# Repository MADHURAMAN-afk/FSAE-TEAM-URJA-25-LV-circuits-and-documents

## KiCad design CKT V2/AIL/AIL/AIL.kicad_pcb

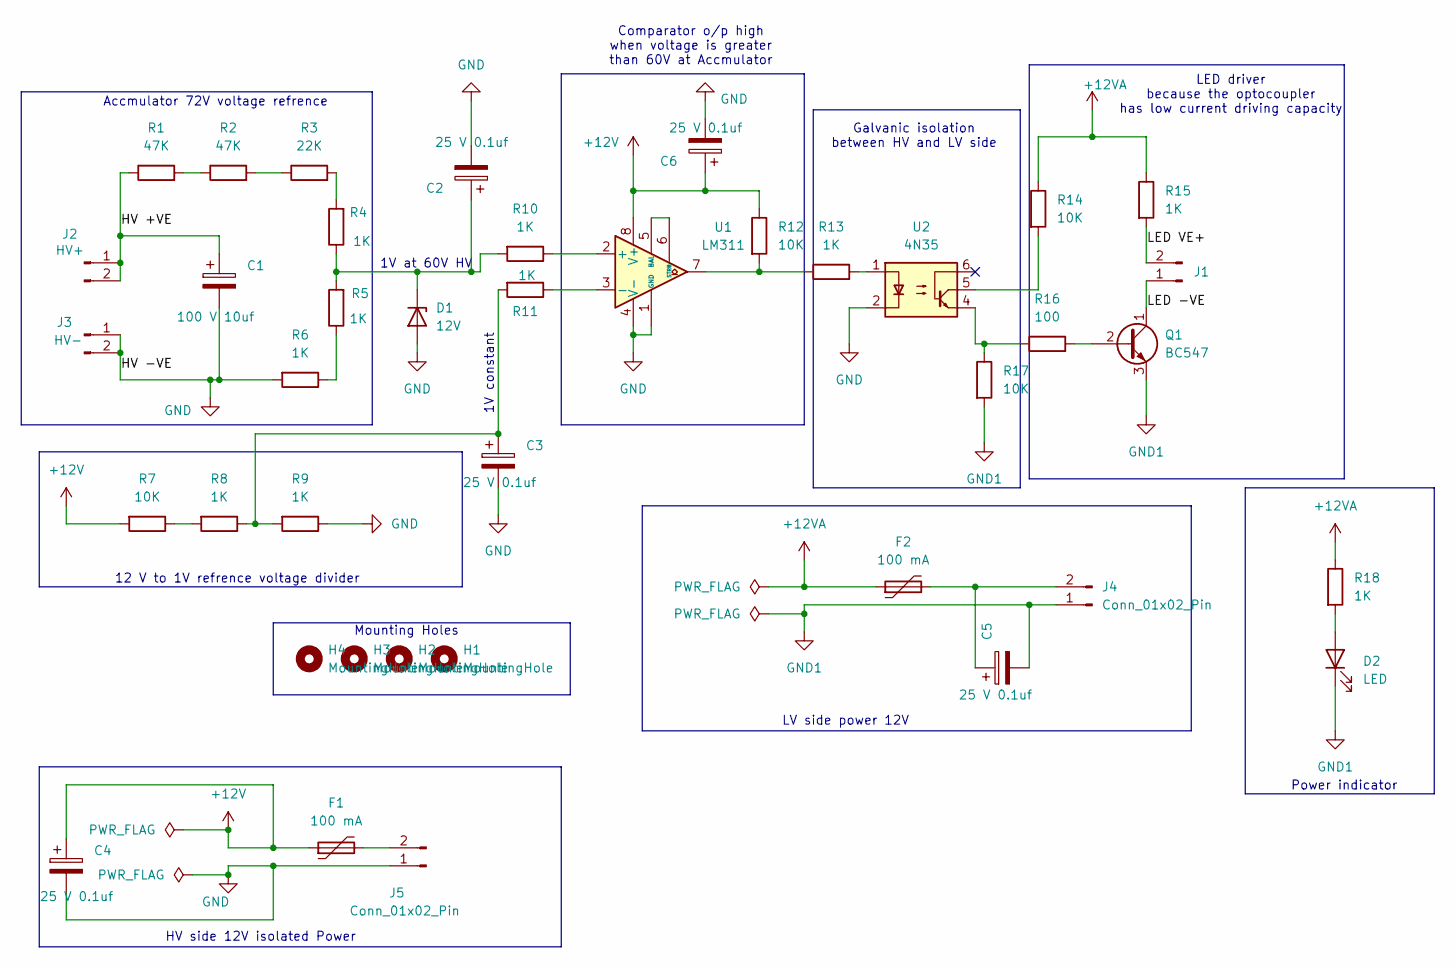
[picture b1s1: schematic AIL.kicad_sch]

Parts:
C1: 100 V 10uf; CP_Radial_D8.0mm_P5.00mm
C2, C3, C4, C5, C6: 25 V 0.1uf; CP_Radial_D8.0mm_P5.00mm
D1: 12V; D_A-405_P10.16mm_Horizontal
D2: LED; LED_D5.0mm
F1, F2: 100 mA; Fuse_BelFuse_0ZRE0008FF_L8.3mm_W3.8mm
H1, H2, H3, H4: MountingHole; MountingHole_4.3mm_M4
J1, J4, J5: Conn_01x02_Pin; TerminalBlock_Phoenix_MKDS-1,5-2-5.08_1x02_P5.08mm_Horizont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
J2: HV+; TerminalBlock_Phoenix_MKDS-1,5-2-5.08_1x02_P5.08mm_Horizont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
J3: HV-; TerminalBlock_Phoenix_MKDS-1,5-2-5.08_1x02_P5.08mm_Horizont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
Q1: BC547; TO-92_Inline
R1, R2: 47K; R_Axial_DIN0204_L3.6mm_D1.6mm_P7.62mm_Horizontal
R3: 22K; R_Axial_DIN0204_L3.6mm_D1.6mm_P7.62mm_Horizontal
R4, R5, R6, R8, R9, R10, R11, R13, R15, R18: 1K; R_Axial_DIN0204_L3.6mm_D1.6mm_P7.62mm_Horizontal
R7, R12, R14, R17: 10K; R_Axial_DIN0204_L3.6mm_D1.6mm_P7.62mm_Horizontal
R16: 100; R_Axial_DIN0204_L3.6mm_D1.6mm_P7.62mm_Horizontal
U1: LM311; CERDIP-8_W7.62mm_SideBrazed_LongPads
U2: 4N35; DIP-6_W7.62mm

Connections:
+12V: C4.1, C6.1, F1.1, R7.2, R12.1, U1.8 (V+)
+12VA: F2.1, R14.1, R15.1, R18.1
/HV +VE: C1.1, J2.1, J2.2, R1.1
/LED -VE: J1.1, Q1.1 (C)
/LED VE+: J1.2, R15.2
GND: C1.2, C2.2, C3.2, C4.2, C6.2, D1.2 (A), J3.1, J3.2, J5.1, R6.2, R9.1, U1.1 (GND), U1.4 (V-), U2.2
GND1: C5.2, D2.1 (K), J4.1, Q1.3 (E), R17.2
unnamed: C3.1, R8.1, R9.2, R11.2
unnamed: C2.1, D1.1 (K), R4.1, R5.2, R10.2
unnamed: D2.2 (A), R18.2
unnamed: C5.1, F2.2, J4.2
unnamed: F1.2, J5.2
unnamed: Q1.2 (B), R16.2
unnamed: R1.2, R2.1
unnamed: R2.2, R3.1
unnamed: R3.2, R4.2
unnamed: R5.1, R6.1
unnamed: R7.1, R8.2
unnamed: R12.2, R13.1, U1.7
unnamed: R13.2, U2.1
unnamed: R14.2, U2.5
unnamed: R16.1, R17.1, U2.4
unnamed: R10.1, U1.2 (+)
unnamed: R11.1, U1.3 (-)
unnamed: U1.5 (BAL), U1.6 (STRB)

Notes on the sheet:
12 V to 1V refrence voltage divider
1V at 60V HV
Power indicator
Galvanic isolation between HV and LV side
Comparator o/p high when voltage is greater than 60V at Accmulator
Accmulator 72V voltage refrence
1V constant
LV side power 12V
Mounting Holes
HV side 12V isolated Power
LED driver because the optocoupler has low current driving capacity

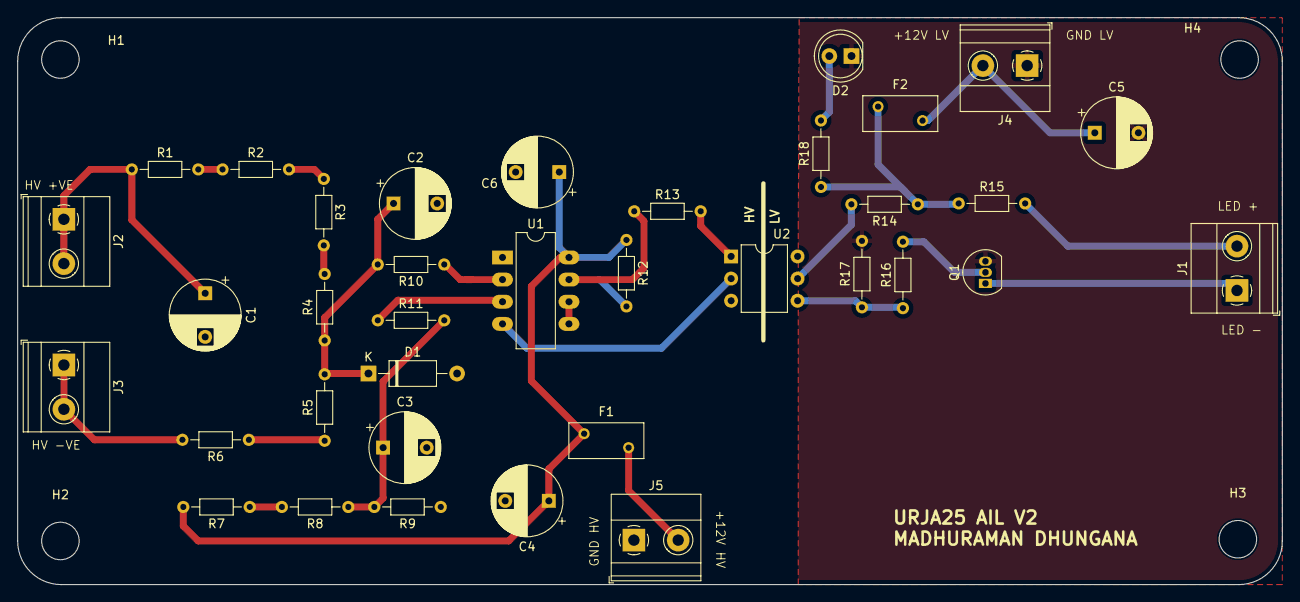
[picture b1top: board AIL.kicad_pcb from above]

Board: 2 copper layers, 145.0 x 65.0 mm, 40 parts (0 on the bottom side), 25 nets.

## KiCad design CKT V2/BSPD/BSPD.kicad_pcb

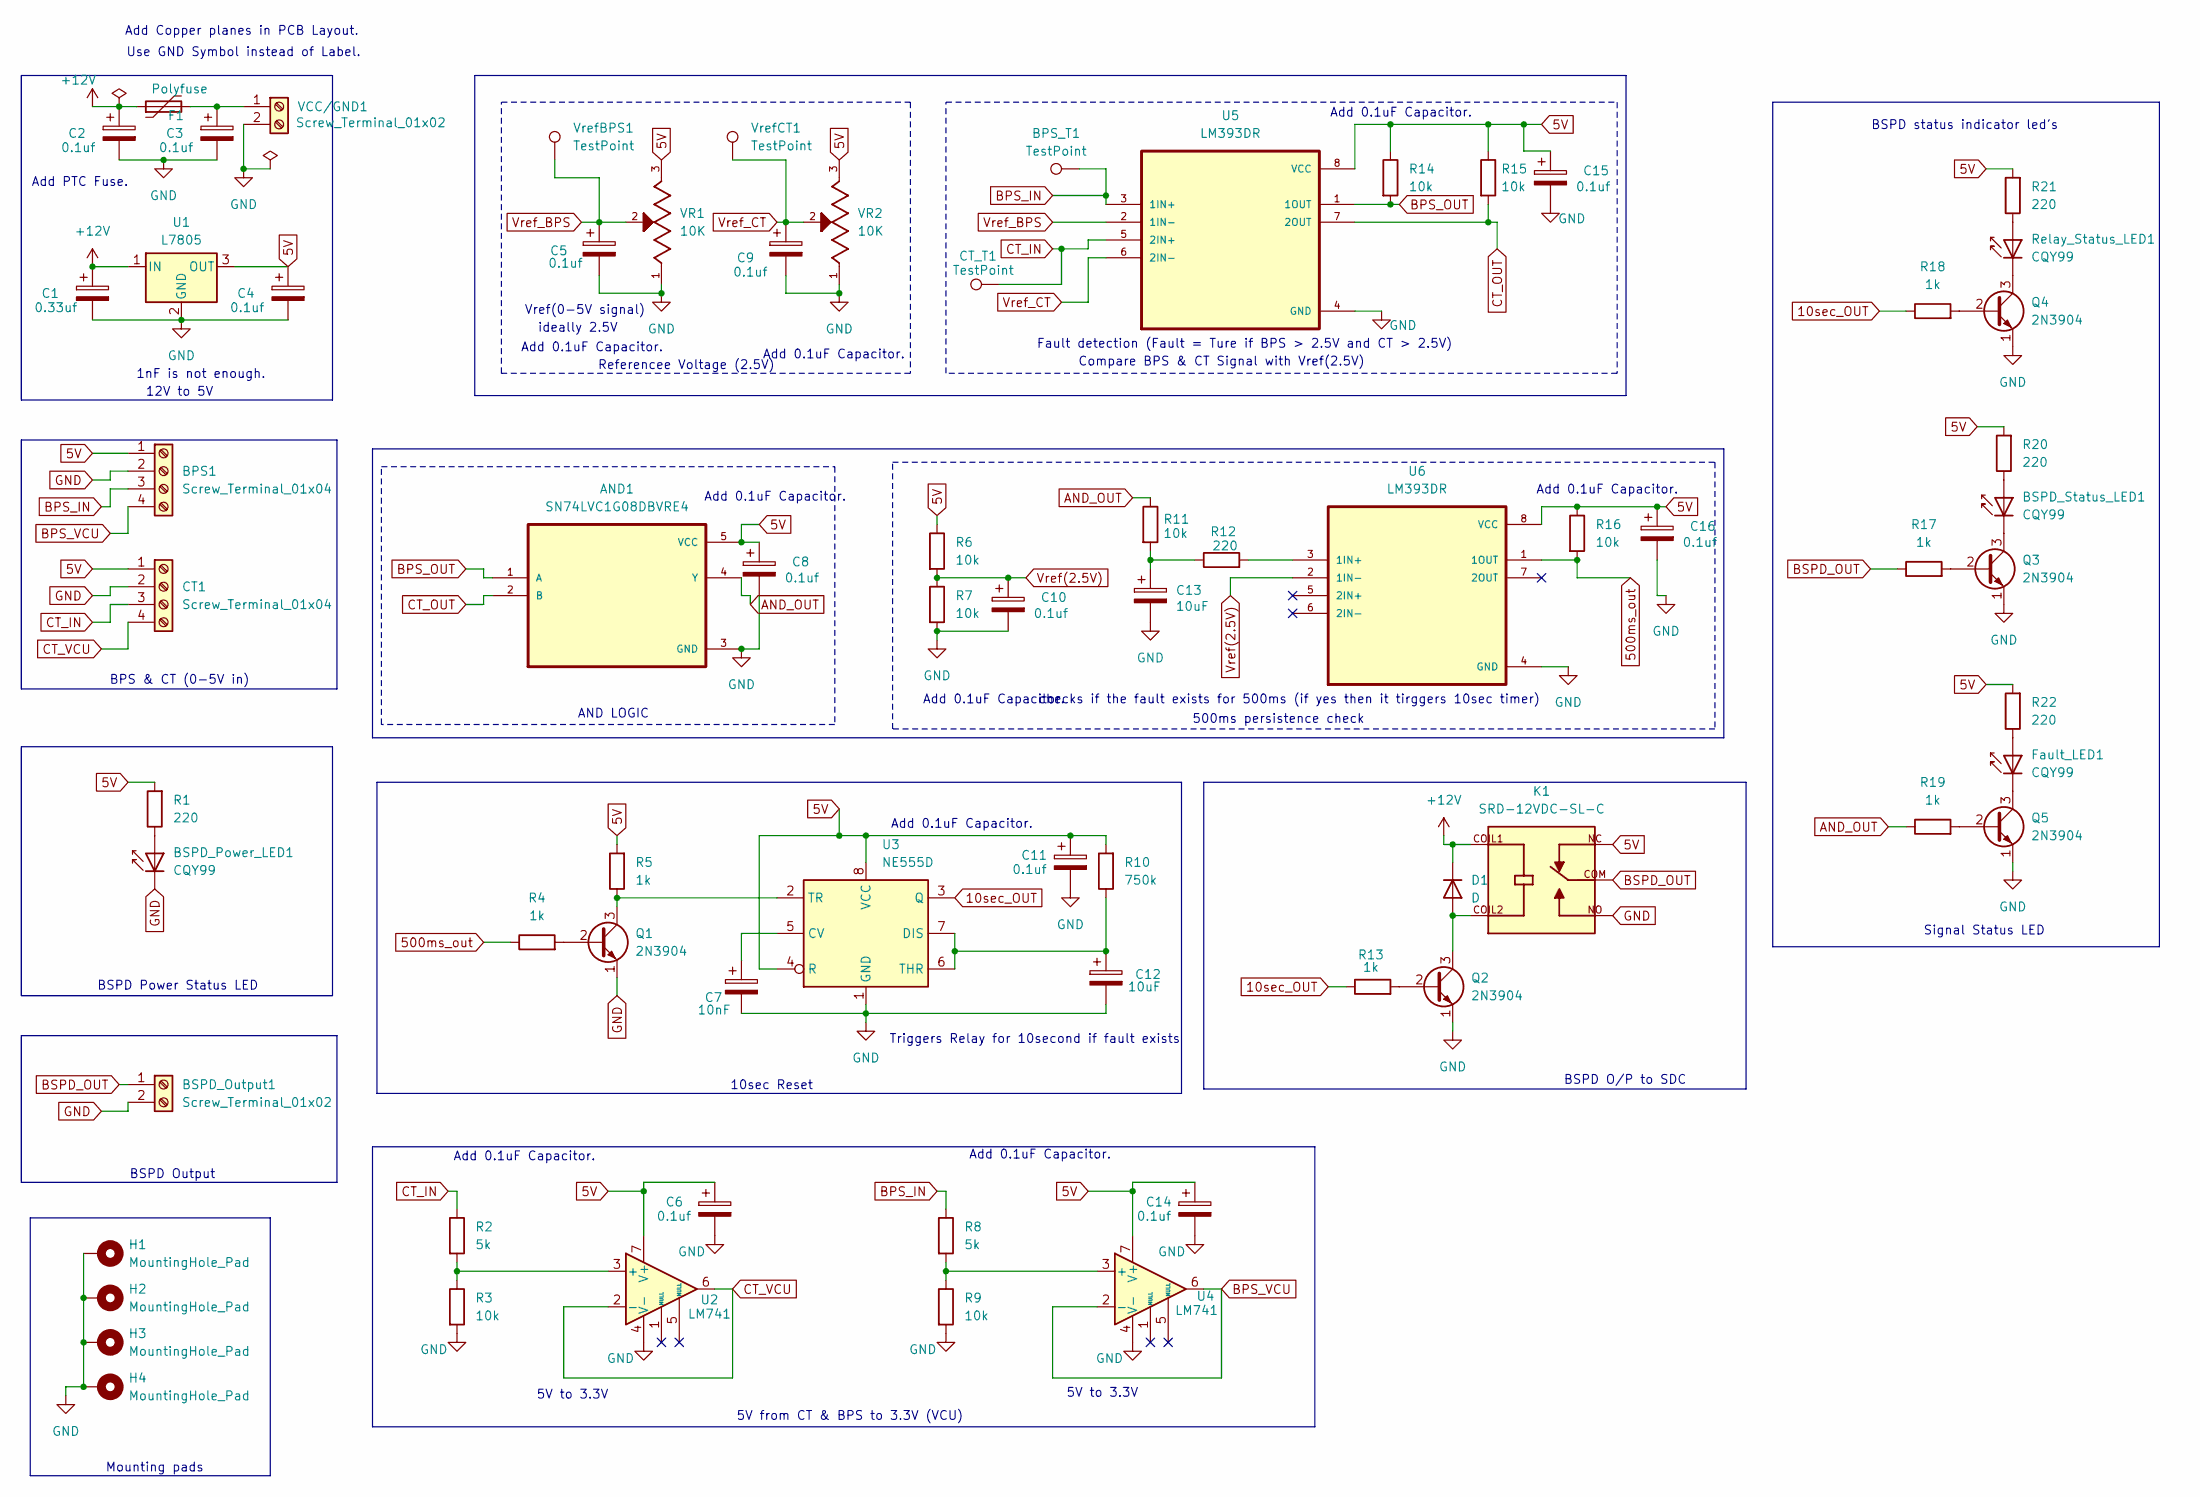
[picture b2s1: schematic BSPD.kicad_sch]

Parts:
AND1: SN74LVC1G08DBVRE4; SOT95P280X145-5N
BPS1: Screw_Terminal_01x04; PinHeader_1x04_P2.54mm_Vertical
BPS_T1: TestPoint; TestPoint_Pad_D1.0mm
BSPD_Output1: Screw_Terminal_01x02; PinHeader_1x02_P2.54mm_Vertical
BSPD_Power_LED1: CQY99; LED_D5.0mm_IRGrey
BSPD_Status_LED1: CQY99; LED_D5.0mm_IRGrey
C1: 0.33uf; CP_Radial_D4.0mm_P2.00mm
C2, C3, C4, C5, C6, C8, C9, C10, C11, C14, C15, C16: 0.1uf; CP_Radial_D4.0mm_P2.00mm
C7: 10nF; CP_Radial_D4.0mm_P2.00mm
C12, C13: 10uF; CP_Radial_D4.0mm_P2.00mm
CT1: Screw_Terminal_01x04; PinHeader_1x04_P2.54mm_Vertical
CT_T1: TestPoint; TestPoint_Pad_D1.0mm
D1: D; D_DO-35_SOD27_P7.62mm_Horizontal
F1: Polyfuse; Fuse_Littelfuse_395Series
Fault_LED1: CQY99; LED_D5.0mm_IRGrey
H1, H2, H3, H4: MountingHole_Pad; MountingHole_2.2mm_M2_ISO7380_Pad
K1: SRD-12VDC-SL-C; RELAY_SRD-12VDC-SL-C; PARTREV 1.0
Q1, Q2, Q3, Q4, Q5: 2N3904; TO-92_Inline
R1, R12, R20, R21, R22: 220; R_Axial_DIN0207_L6.3mm_D2.5mm_P10.16mm_Horizontal
R2, R8: 5k; R_Axial_DIN0207_L6.3mm_D2.5mm_P10.16mm_Horizontal
R3, R6, R7, R9, R11, R14, R15, R16: 10k; R_Axial_DIN0207_L6.3mm_D2.5mm_P10.16mm_Horizontal
R4, R5, R13, R17, R18, R19: 1k; R_Axial_DIN0207_L6.3mm_D2.5mm_P10.16mm_Horizontal
R10: 750k; R_Axial_DIN0207_L6.3mm_D2.5mm_P10.16mm_Horizontal
Relay_Status_LED1: CQY99; LED_D5.0mm_IRGrey
U1: L7805; TO-220F-3_Horizontal_TabUp
U2, U4: LM741; DIP794W45P254L959H508Q8
U3: NE555D; DIP254P762X533-8
U5, U6: LM393DR; DIP794W45P254L959H508Q8
VCC/GND1: Screw_Terminal_01x02; PinHeader_1x02_P2.54mm_Vertical
VR1, VR2: 10K; TRIM_3296W-OT1-103LF; PARTREV 05/16
VrefBPS1: TestPoint; TestPoint_Pad_D1.0mm
VrefCT1: TestPoint; TestPoint_Pad_D1.0mm

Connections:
5V: AND1.5 (VCC), BPS1.1, C4.1, C6.1, C8.1, C11.1, C14.1, C15.1, C16.1, CT1.1, K1.NC, R1.2, R5.2, R6.1, R10.2, R14.1, R15.1, R16.1, R20.2, R21.2, R22.2, U1.3 (OUT), U2.7 (V+), U3.4 (R), U3.8 (VCC), U4.7 (V+), U5.8 (VCC), U6.8 (VCC), VR1.3, VR2.3
10sec_OUT: R13.1, R18.1, U3.3 (Q)
500ms_out: R4.1, R16.2, U6.1 (1OUT)
+12V: C1.1, C2.1, D1.1 (K), F1.1, K1.COIL1, U1.1 (IN)
AND_OUT: AND1.4 (Y), R11.1, R19.1
BPS_IN: BPS1.3, BPS_T1.1, R8.1, U5.3 (1IN+)
BPS_OUT: AND1.1 (A), R14.2, U5.1 (1OUT)
BPS_VCU: BPS1.4, U4.2 (-), U4.6
BSPD_OUT: BSPD_Output1.1, K1.COM, R17.1
CT_IN: CT1.3, CT_T1.1, R2.1, U5.5 (2IN+)
CT_OUT: AND1.2 (B), R15.2, U5.7 (2OUT)
CT_VCU: CT1.4, U2.2 (-), U2.6
GND: AND1.3 (GND), BPS1.2, BSPD_Output1.2, BSPD_Power_LED1.1 (K), C1.2, C2.2, C3.2, C4.2, C5.2, C6.2, C7.2, C8.2, C9.2, C10.2, C11.2, C12.2, C13.2, C14.2, C15.2, C16.2, CT1.2, H1.1, H2.1, H3.1, H4.1, K1.NO, Q1.1 (E), Q2.1 (E), Q3.1 (E), Q4.1 (E), Q5.1 (E), R3.2, R7.2, R9.2, U1.2 (GND), U2.4 (V-), U3.1 (GND), U4.4 (V-), U5.4 (GND), U6.4 (GND), VCC/GND1.2, VR1.1, VR2.1
unnamed: BSPD_Power_LED1.2 (A), R1.1
unnamed: BSPD_Status_LED1.2 (A), R20.1
unnamed: BSPD_Status_LED1.1 (K), Q3.3 (C)
unnamed: C13.1, R11.2, R12.1
unnamed: D1.2 (A), K1.COIL2, Q2.3 (C)
unnamed: Fault_LED1.2 (A), R22.1
unnamed: Fault_LED1.1 (K), Q5.3 (C)
unnamed: Q1.2 (B), R4.2
unnamed: Q1.3 (C), R5.1, U3.2 (TR)
unnamed: Q2.2 (B), R13.2
unnamed: Q3.2 (B), R17.2
unnamed: Q4.2 (B), R18.2
unnamed: Q4.3 (C), Relay_Status_LED1.1 (K)
unnamed: Q5.2 (B), R19.2
unnamed: R21.1, Relay_Status_LED1.2 (A)
unnamed: R2.2, R3.1, U2.3 (+)
unnamed: C7.1, U3.5 (CV)
unnamed: C12.1, R10.1, U3.6 (THR), U3.7 (DIS)
unnamed: R8.2, R9.1, U4.3 (+)
unnamed: R12.2, U6.3 (1IN+)
unnamed: C3.1, F1.2, VCC/GND1.1
Vref(2.5V): C10.1, R6.2, R7.1, U6.2 (1IN-)
Vref_BPS: C5.1, U5.2 (1IN-), VR1.2, VrefBPS1.1
Vref_CT: C9.1, U5.6 (2IN-), VR2.2, VrefCT1.1

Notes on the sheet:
Triggers Relay for 10second if fault exists
BSPD Power Status LED
AND LOGIC
Add Copper planes in PCB Layout.
5V to 3.3V
BSPD O/P to SDC
checks if the fault exists for 500ms (if yes then it tirggers 10sec timer)
10sec Reset
Add 0.1uF Capacitor.
BPS & CT (0-5V in)
Fault detection (Fault = Ture if BPS > 2.5V and CT > 2.5V)
12V to 5V
Signal Status LED
Compare BPS & CT Signal with Vref(2.5V)
5V from CT & BPS to 3.3V (VCU)
Vref(0-5V signal)
BSPD status indicator led's
ideally 2.5V
Add PTC Fuse.
1nF is not enough.
Referencee Voltage (2.5V)
BSPD Output
Mounting pads
500ms persistence check
Use GND Symbol instead of Label.

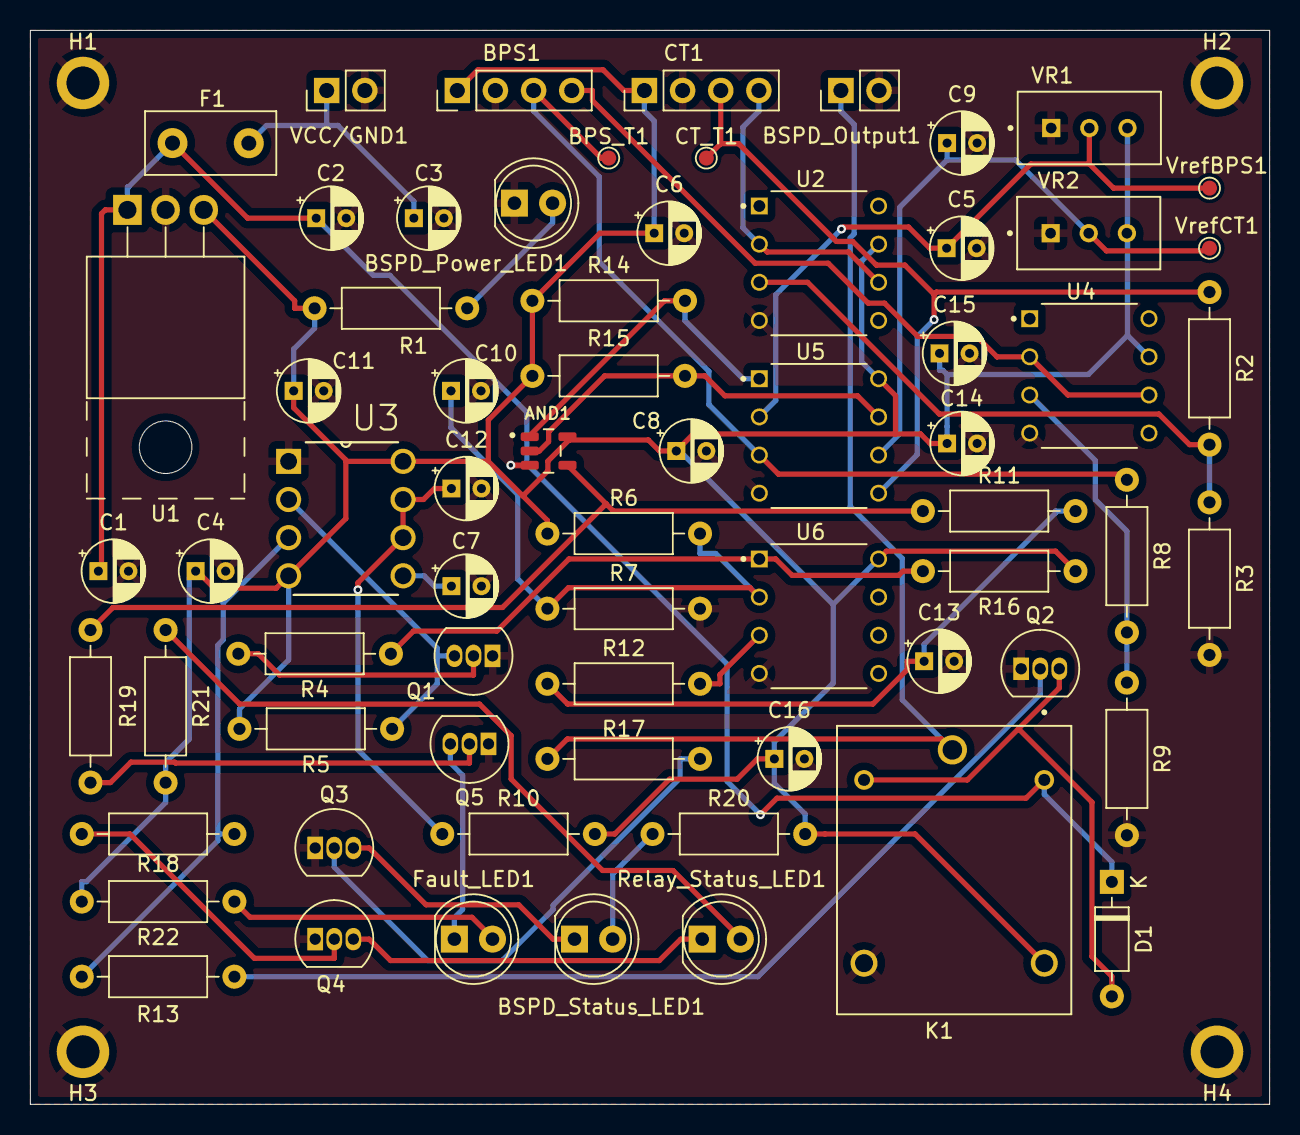
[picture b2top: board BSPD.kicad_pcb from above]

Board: 2 copper layers, 82.5 x 71.5 mm, 71 parts (0 on the bottom side), 37 nets.

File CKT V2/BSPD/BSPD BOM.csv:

"Reference","Value","Datasheet","Footprint","Qty","DNP"
"AND1","SN74LVC1G08DBVRE4","","Single AND Gate:SOT95P280X145-5N","1",""
"BPS1,CT1","Screw_Terminal_01x04","~","Connector_PinHeader_2.54mm:PinHeader_1x04_P2.54mm_Vertical","2",""
"BPS_T1,CT_T1,VrefBPS1,VrefCT1","TestPoint","~","TestPoint:TestPoint_Pad_D1.0mm","4",""
"BSPD_Output1,VCC/GND1","Screw_Terminal_01x02","~","Connector_PinHeader_2.54mm:PinHeader_1x02_P2.54mm_Vertical","2",""
"BSPD_Power_LED1,BSPD_Status_LED1,Fault_LED1,Relay_Status_LED1","CQY99","https://www.prtice.info/IMG/pdf/CQY99.pdf","LED_THT:LED_D5.0mm_IRGrey","4",""
"C1","0.33uf","~","Capacitor_THT:CP_Radial_D4.0mm_P2.00mm","1",""
"C2,C3,C4,C5,C6,C8,C9,C10,C11,C14,C15,C16","0.1uf","~","Capacitor_THT:CP_Radial_D4.0mm_P2.00mm","12",""
"C7","10nF","~","Capacitor_THT:CP_Radial_D4.0mm_P2.00mm","1",""
"C12,C13","10uF","~","Capacitor_THT:CP_Radial_D4.0mm_P2.00mm","2",""
"D1","D","~","Diode_THT:D_DO-35_SOD27_P7.62mm_Horizontal","1",""
"F1","Polyfuse","~","Fuse:Fuse_Littelfuse_395Series","1",""
"K1","SRD-12VDC-SL-C","","Relay SPDT 12V:RELAY_SRD-12VDC-SL-C","1",""
"Q1,Q2,Q3,Q4,Q5","2N3904","https://www.onsemi.com/pub/Collateral/2N3903-D.PDF","Package_TO_SOT_THT:TO-92_Inline","5",""
"R1,R12,R20,R21,R22","220","~","Resistor_THT:R_Axial_DIN0207_L6.3mm_D2.5mm_P10.16mm_Horizontal","5",""
"R2,R8","5k","~","Resistor_THT:R_Axial_DIN0207_L6.3mm_D2.5mm_P10.16mm_Horizontal","2",""
"R3,R6,R7,R9,R11,R14,R15,R16","10k","~","Resistor_THT:R_Axial_DIN0207_L6.3mm_D2.5mm_P10.16mm_Horizontal","8",""
"R4,R5,R13,R17,R18,R19","1k","~","Resistor_THT:R_Axial_DIN0207_L6.3mm_D2.5mm_P10.16mm_Horizontal","6",""
"R10","750k","~","Resistor_THT:R_Axial_DIN0207_L6.3mm_D2.5mm_P10.16mm_Horizontal","1",""
"U1","L7805","http://www.st.com/content/ccc/resource/technical/document/da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","Package_TO_SOT_THT:TO-220F-3_Horizontal_TabUp","1",""
"U2,U4","LM741","http://www.ti.com/lit/ds/symlink/lm741.pdf","LM741CN_NOPB:DIP794W45P254L959H508Q8","2",""
"U3","NE555D","http://www.ti.com/lit/ds/symlink/ne555.pdf","NE555:DIP254P762X533-8","1",""
"U5,U6","LM393DR","","LM393_THT:DIP794W45P254L959H508Q8","2",""
"VR1,VR2","10K","","Trimmer Pot:TRIM_3296W-OT1-103LF","2",""

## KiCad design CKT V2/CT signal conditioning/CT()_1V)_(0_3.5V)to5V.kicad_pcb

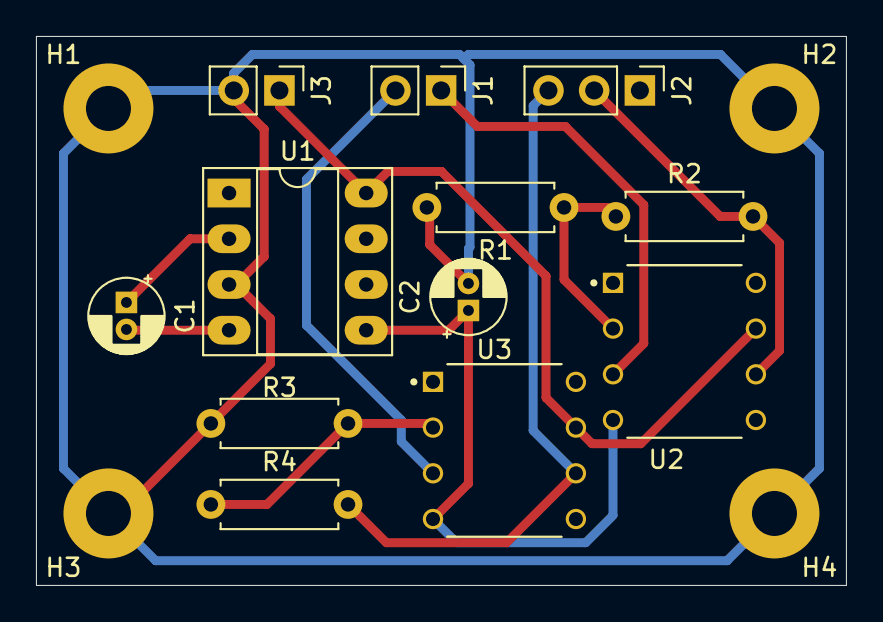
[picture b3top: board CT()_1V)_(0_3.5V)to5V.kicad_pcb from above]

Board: 2 copper layers, 45.0 x 30.5 mm, 16 parts (0 on the bottom side), 11 nets.

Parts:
C1, C2: 10uf; CP_Radial_D4.0mm_P1.50mm
H1, H2, H3, H4: MountingHole_Pad; MountingHole_2.5mm_Pad
J1: CT_O/P; PinHeader_1x02_P2.54mm_Vertical
J2: O/P jumper; PinHeader_1x03_P2.54mm_Vertical
J3: power; PinHeader_1x02_P2.54mm_Vertical
R1, R3: 10k; R_Axial_DIN0207_L6.3mm_D2.5mm_P7.62mm_Horizontal
R2: 40k; R_Axial_DIN0207_L6.3mm_D2.5mm_P7.62mm_Horizontal
R4: 4k; R_Axial_DIN0207_L6.3mm_D2.5mm_P7.62mm_Horizontal
U1: ICL7660; DIP-8_W7.62mm_Socket_LongPads
U2, U3: LM741; DIP794W45P254L959H508Q8

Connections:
0-1V: J1.1, U2.3 (+)
0-3.5V: J1.2, U3.3 (+)
0_1V_O/P: J2.2, R2.2, U2.6
0_3.5V_O/P: J2.3, R4.2, U3.6
+12V: J3.1, U1.8 (V+), U2.7 (V+), U3.7 (V+)
-12V: C2.1, U1.5 (VOUT), U2.4 (V-), U3.4 (V-)
GND: C2.2, H1.1, H2.1, H3.1, H4.1, J3.2, R1.2, R3.2, U1.3 (GND)
unnamed: C1.1, U1.2 (CAP+)
unnamed: C1.2, U1.4 (CAP-)
unnamed: R1.1, R2.1, U2.2 (-)
unnamed: R3.1, R4.1, U3.2 (-)

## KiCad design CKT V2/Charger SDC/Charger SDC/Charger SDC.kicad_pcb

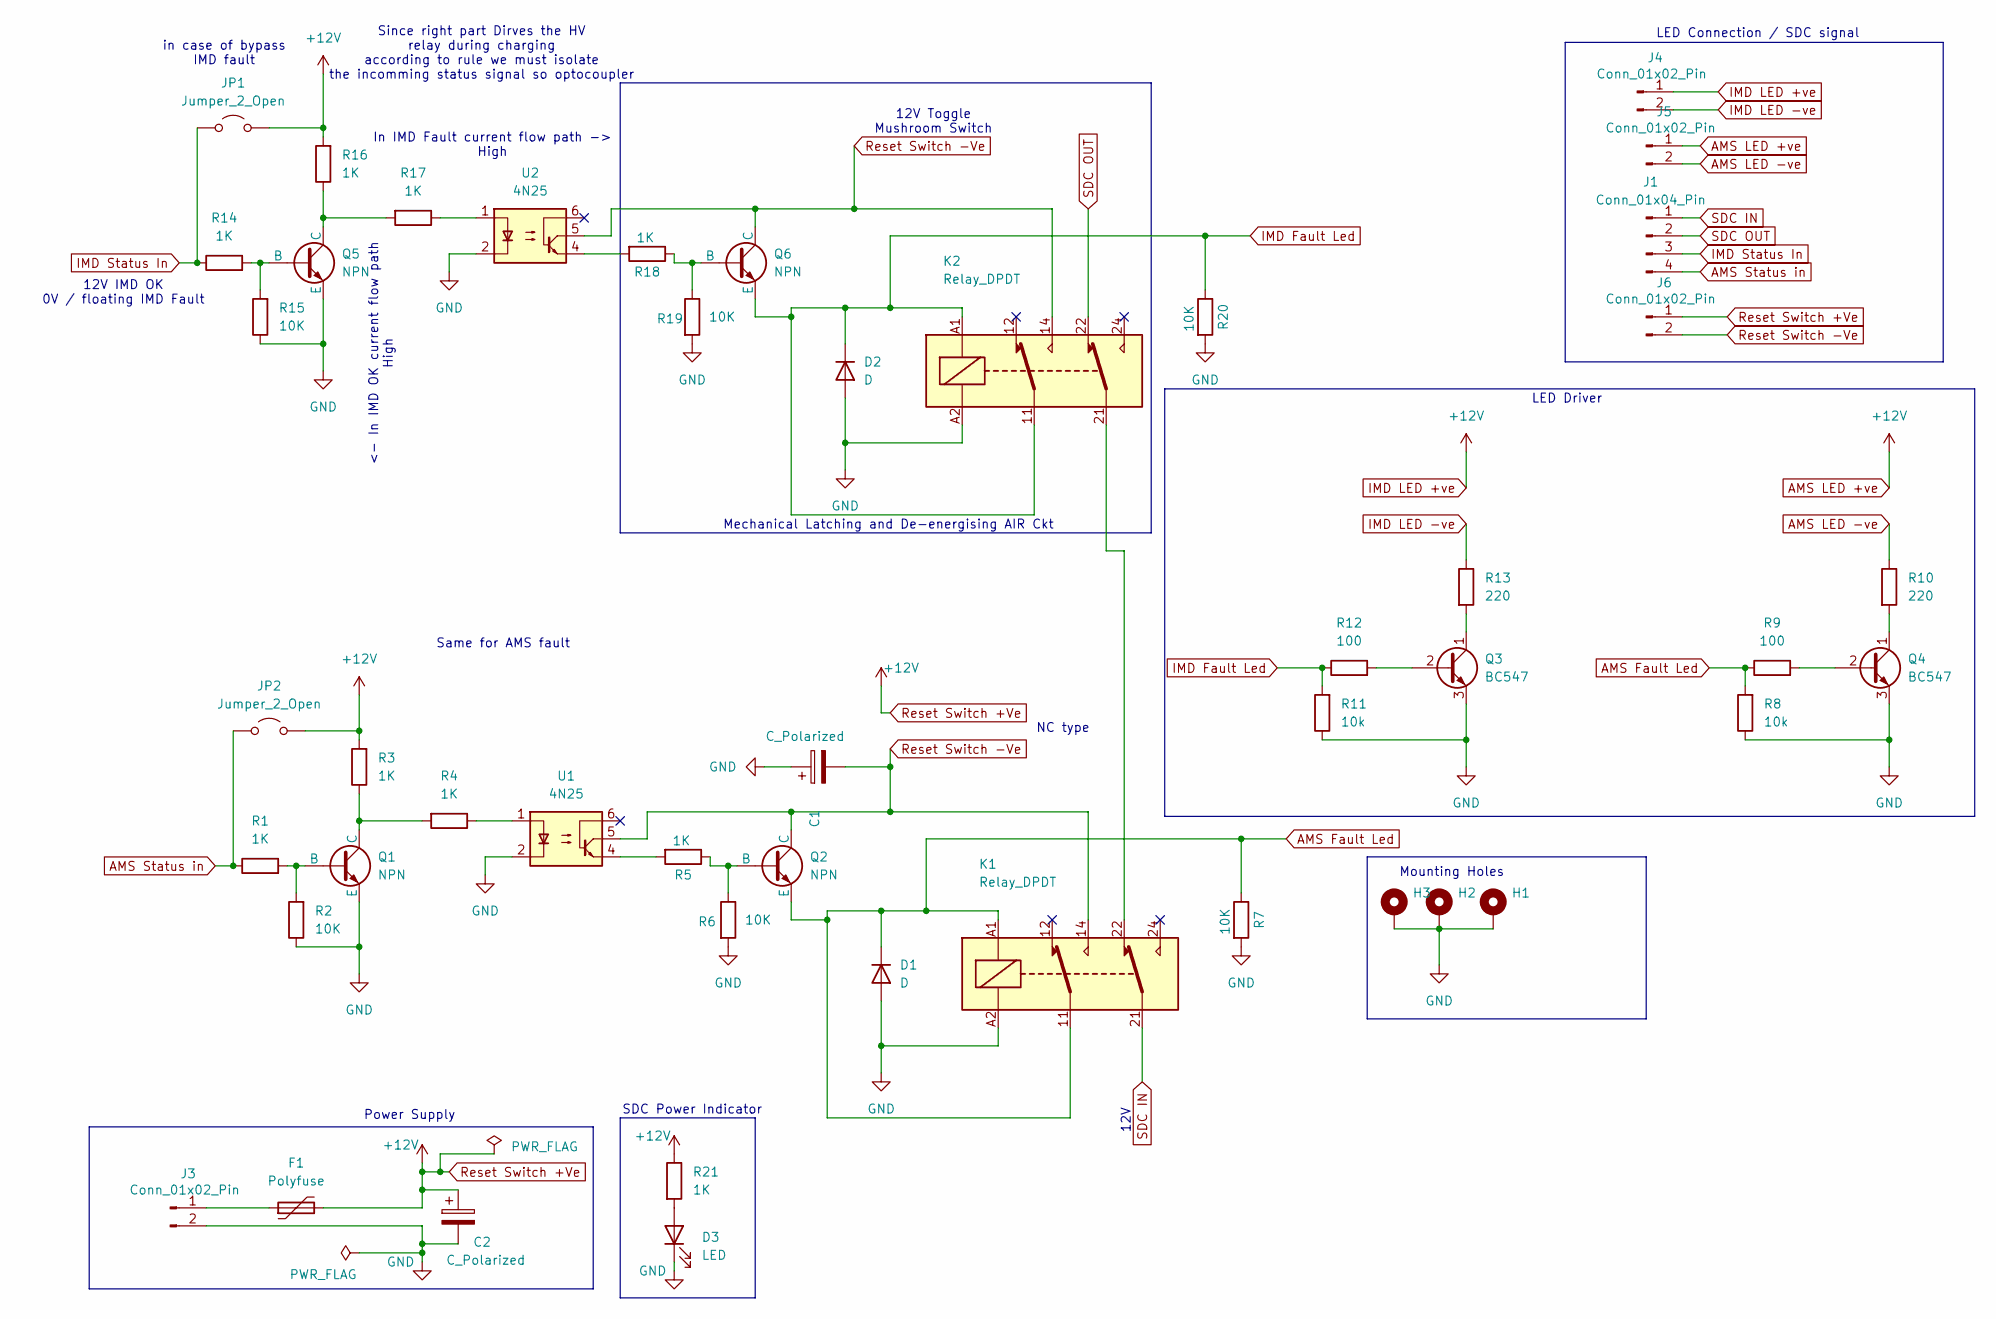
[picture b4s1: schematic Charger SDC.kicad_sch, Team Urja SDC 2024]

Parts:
C1, C2: C_Polarized; CP_Radial_D12.5mm_P7.50mm
D1, D2: D; D_A-405_P7.62mm_Horizontal
D3: LED; LED_D5.0mm
F1: Polyfuse; Fuse_BelFuse_0ZRE0008FF_L8.3mm_W3.8mm
H1, H2, H3: MountingHole_Pad; MountingHole_3.2mm_M3_DIN965_Pad
J1: Conn_01x04_Pin; PinHeader_1x04_P2.54mm_Vertical
J3, J4, J5, J6: Conn_01x02_Pin; PinHeader_1x02_P2.54mm_Vertical
JP1, JP2: Jumper_2_Open; PinHeader_1x02_P2.54mm_Vertical
K1, K2: Relay_DPDT; Relay_DPDT_Finder_40.52
Q1, Q5: NPN; TO-92L_Inline_Wide
Q2, Q6: NPN; TO-92_Inline_Wide
Q3, Q4: BC547; TO-92_Inline
R1, R3, R4, R5, R14, R16, R17, R18, R21: 1K; R_Axial_DIN0207_L6.3mm_D2.5mm_P7.62mm_Horizontal
R2, R6, R7, R15, R19, R20: 10K; R_Axial_DIN0207_L6.3mm_D2.5mm_P7.62mm_Horizontal
R8, R11: 10k; R_Axial_DIN0204_L3.6mm_D1.6mm_P7.62mm_Horizontal
R9, R12: 100; R_Axial_DIN0204_L3.6mm_D1.6mm_P7.62mm_Horizontal
R10, R13: 220; R_Axial_DIN0204_L3.6mm_D1.6mm_P7.62mm_Horizontal
U1, U2: 4N25; DIP-6_W7.62mm

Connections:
AMS Fault Led: D1.1 (K), K1.11, K1.A1, Q2.3 (E), R7.1, R8.2, R9.1
AMS LED +ve: C2.1, F1.2, J4.1, J5.1, J6.1, JP1.2 (B), JP2.2 (B), R3.2, R16.2, R21.1
AMS LED -ve: J5.2, R10.1
AMS Status in: J1.4, JP2.1 (A), R1.1
GND: C1.1, C2.2, D1.2 (A), D2.2 (A), D3.1 (K), H1.1, H2.1, H3.1, J3.2, K1.A2, K2.A2, Q1.3 (E), Q3.3 (E), Q4.3 (E), Q5.3 (E), R2.1, R6.2, R7.2, R8.1, R11.1, R15.1, R19.2, R20.2, U1.2, U2.2
IMD Fault Led: D2.1 (K), K2.11, K2.A1, Q6.3 (E), R11.2, R12.1, R20.1
IMD LED -ve: J4.2, R13.1
IMD Status In: J1.3, JP1.1 (A), R14.1
unnamed: D3.2 (A), R21.2
unnamed: F1.1, J3.1
unnamed: K1.22, K2.21
unnamed: Q1.2 (B), R1.2, R2.2
unnamed: Q1.1 (C), R3.1, R4.2
unnamed: Q2.2 (B), R5.1, R6.1
unnamed: Q3.2 (B), R12.2
unnamed: Q3.1 (C), R13.2
unnamed: Q4.2 (B), R9.2
unnamed: Q4.1 (C), R10.2
unnamed: Q5.2 (B), R14.2, R15.2
unnamed: Q5.1 (C), R16.1, R17.2
unnamed: Q6.2 (B), R18.1, R19.1
unnamed: R4.1, U1.1
unnamed: R5.2, U1.4
unnamed: R17.1, U2.1
unnamed: R18.2, U2.4
Reset Switch -Ve: C1.2, J6.2, K1.14, K2.14, Q2.1 (C), Q6.1 (C), U1.5, U2.5
SDC IN: J1.1, K1.21
SDC OUT: J1.2, K2.22

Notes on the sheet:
Power Supply
LED Connection / SDC signal
LED Driver
Same for AMS fault
12V Toggle Mushroom Switch
in case of bypass IMD fault
Mechanical Latching and De-energising AIR Ckt
In IMD Fault current flow path -> High
Since right part Dirves the HV relay during charging according to rule we must isolate the incomming status signal so optocoupler
NC type
12V IMD OK 0V / floating IMD Fault
Mounting Holes
SDC Power Indicator
12V
<- In IMD OK current flow path High

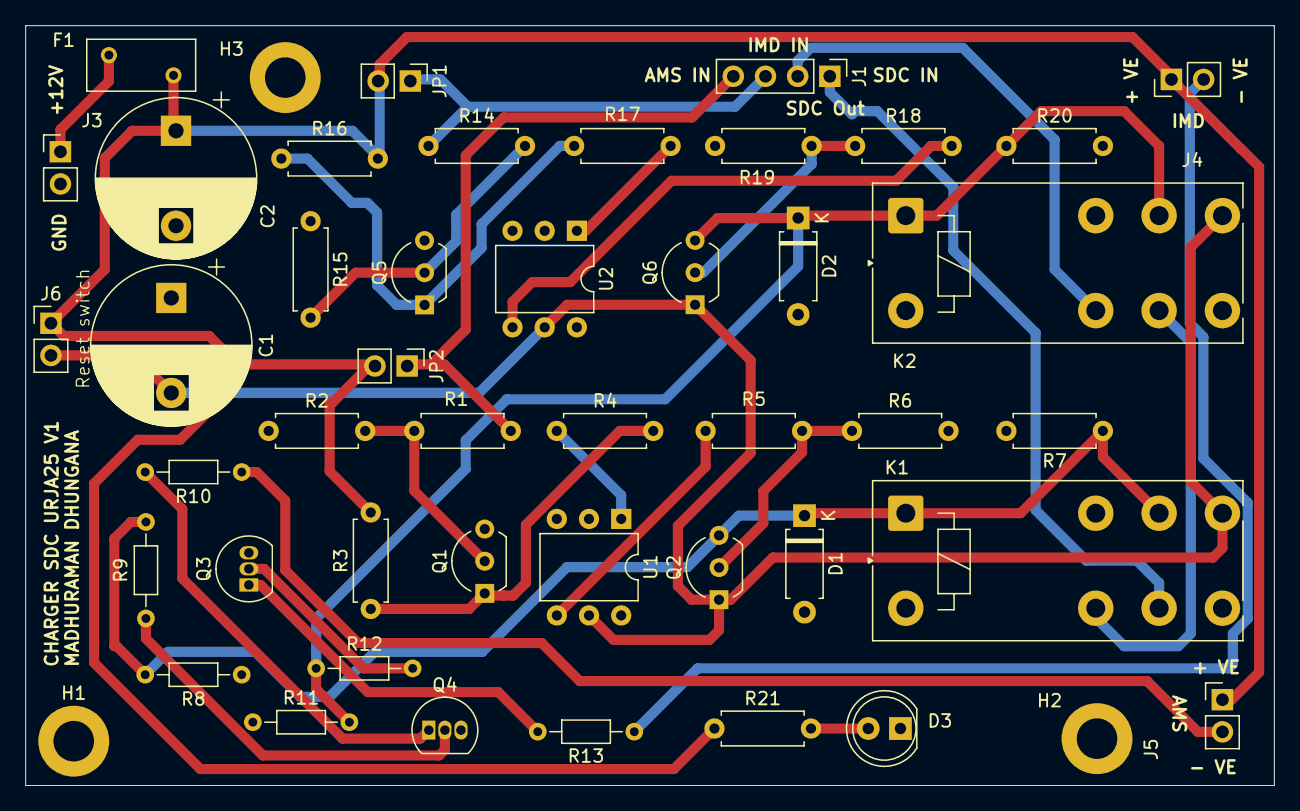
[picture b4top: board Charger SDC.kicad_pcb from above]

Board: 2 copper layers, 98.6 x 60.0 mm, 47 parts (0 on the bottom side), 28 nets.

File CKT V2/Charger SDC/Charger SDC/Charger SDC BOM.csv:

Reference,Value,Footprint,Qty,DNP
"C1,C2",C_Polarized,Capacitor_THT:CP_Radial_D12.5mm_P7.50mm,2,
"D1,D2",D,Diode_THT:D_A-405_P7.62mm_Horizontal,2,
D3,LED,LED_THT:LED_D5.0mm,1,
F1,Polyfuse,Fuse:Fuse_BelFuse_0ZRE0008FF_L8.3mm_W3.8mm,1,
J1,Conn_01x04_Pin,Connector_PinHeader_2.54mm:PinHeader_1x04_P2.54mm_Vertical,1,
"J3,J4,J5,J6",Conn_01x02_Pin,Connector_PinHeader_2.54mm:PinHeader_1x02_P2.54mm_Vertical,4,
"JP1,JP2",Jumper_2_Open,Connector_PinHeader_2.54mm:PinHeader_1x02_P2.54mm_Vertical,2,
"K1,K2",Relay_DPDT,Relay_THT:Relay_DPDT_Finder_40.52,2,
"Q1,Q2,Q5,Q6",NPN,-- mixed values --,4,
"Q3,Q4",BC547,Package_TO_SOT_THT:TO-92_Inline,2,
"R1,R3,R4,R5,R14,R16,R17,R18,R21",1K,Resistor_THT:R_Axial_DIN0207_L6.3mm_D2.5mm_P7.62mm_Horizontal,9,
"R2,R6,R7,R15,R19,R20",10K,Resistor_THT:R_Axial_DIN0207_L6.3mm_D2.5mm_P7.62mm_Horizontal,6,
"R8,R11",10k,Resistor_THT:R_Axial_DIN0204_L3.6mm_D1.6mm_P7.62mm_Horizontal,2,
"R9,R12",100,Resistor_THT:R_Axial_DIN0204_L3.6mm_D1.6mm_P7.62mm_Horizontal,2,
"R10,R13",220,Resistor_THT:R_Axial_DIN0204_L3.6mm_D1.6mm_P7.62mm_Horizontal,2,
"U1,U2",4N25,Package_DIP:DIP-6_W7.62mm,2,

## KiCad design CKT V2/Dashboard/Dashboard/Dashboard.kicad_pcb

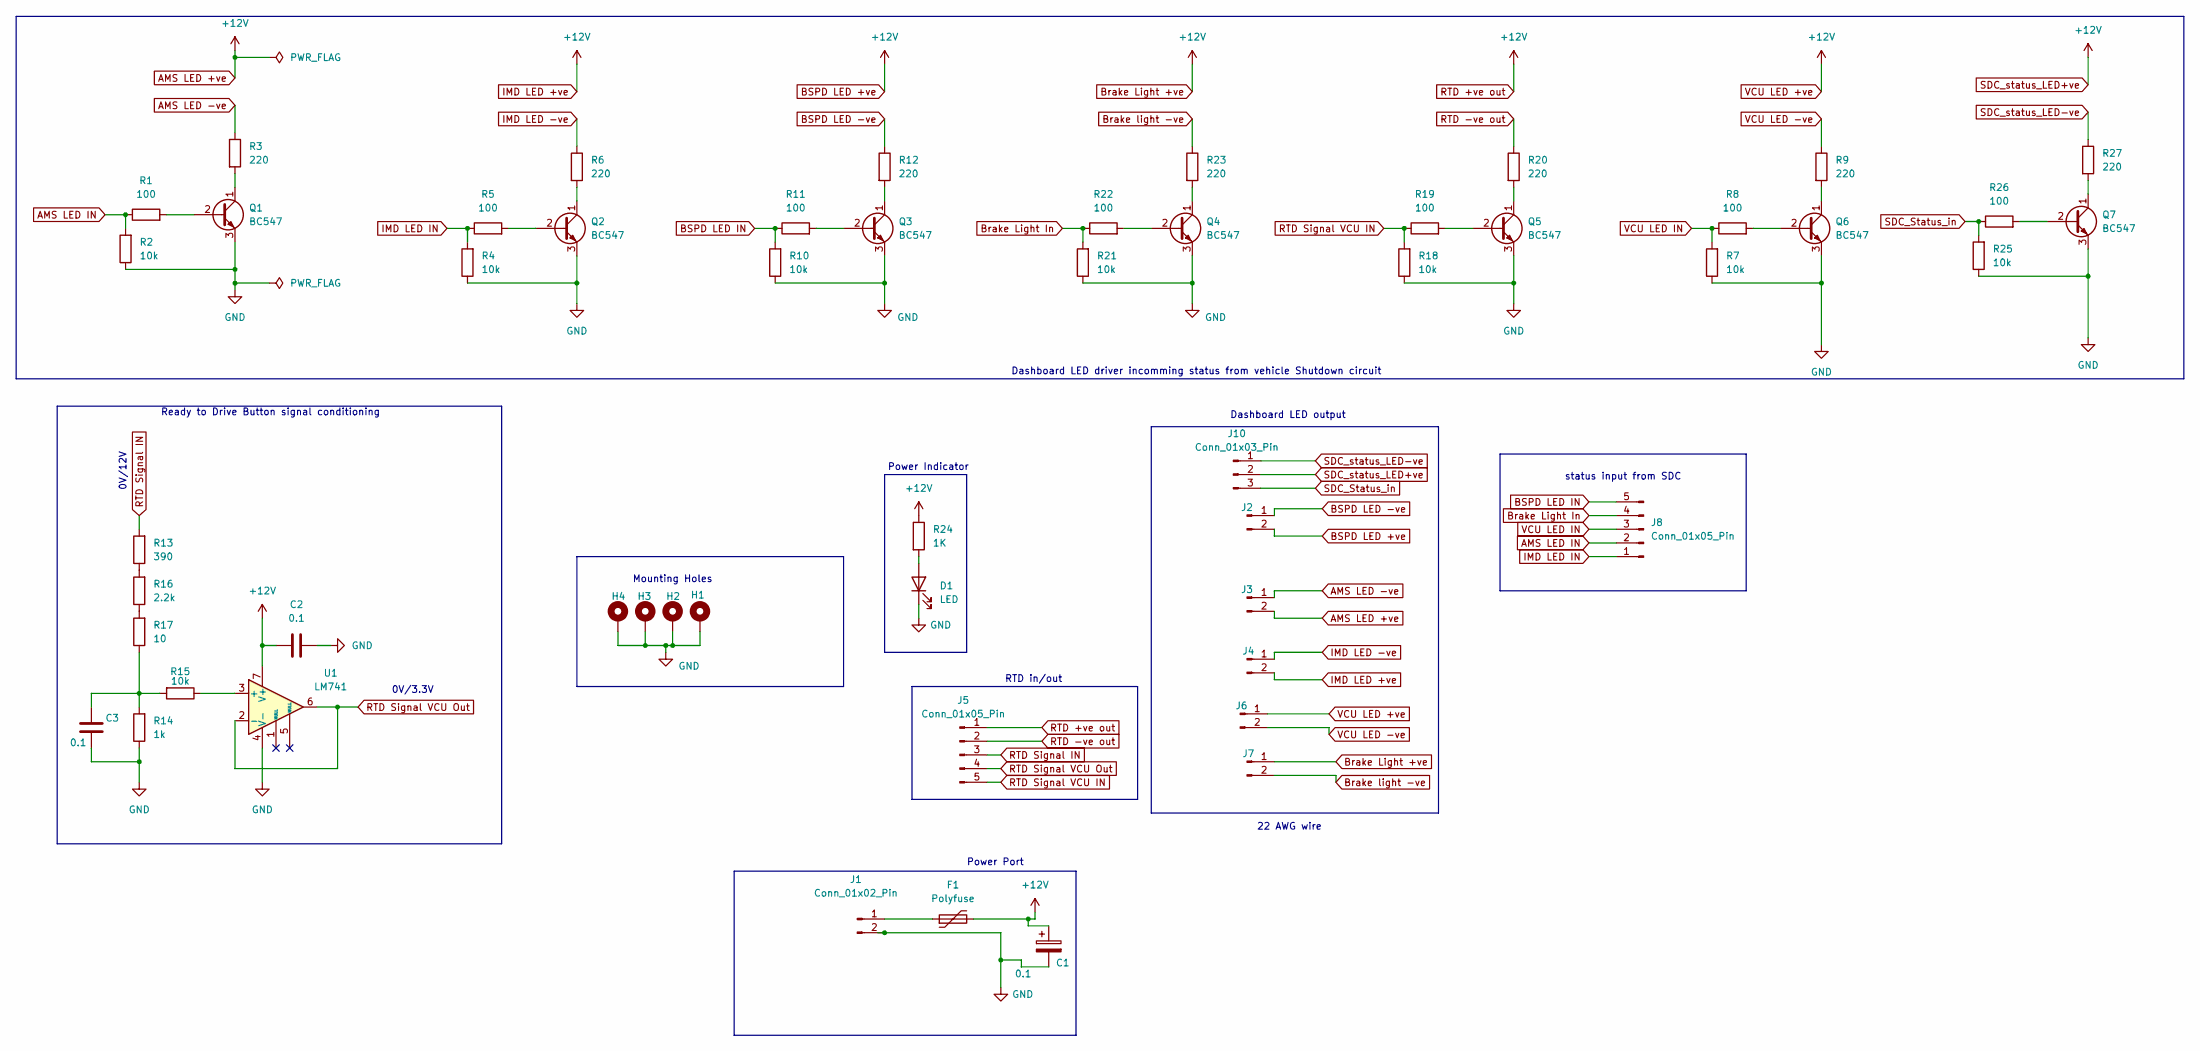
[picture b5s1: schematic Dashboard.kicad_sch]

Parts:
C1, C2, C3: 0.1; CP_Radial_D8.0mm_P5.00mm
D1: LED; LED_D5.0mm
F1: Polyfuse; Fuse_BelFuse_0ZRE0008FF_L8.3mm_W3.8mm
H1, H2, H3, H4: MountingHole_Pad_MP; MountingHole_3.2mm_M3_ISO7380_Pad
J1, J2, J3, J4, J6, J7: Conn_01x02_Pin; PinHeader_1x02_P2.54mm_Vertical
J5, J8: Conn_01x05_Pin; PinHeader_1x05_P2.54mm_Vertical
J10: Conn_01x03_Pin; PinHeader_1x03_P2.54mm_Vertical
Q1, Q2, Q3, Q4, Q5, Q6, Q7: BC547; TO-92_Inline
R1, R5, R8, R11, R19, R22, R26: 100; R_Axial_DIN0204_L3.6mm_D1.6mm_P7.62mm_Horizontal
R2, R4, R7, R10, R15, R18, R21, R25: 10k; R_Axial_DIN0204_L3.6mm_D1.6mm_P7.62mm_Horizontal
R3, R6, R9, R12, R20, R23, R27: 220; R_Axial_DIN0204_L3.6mm_D1.6mm_P7.62mm_Horizontal
R13: 390; R_Axial_DIN0204_L3.6mm_D1.6mm_P7.62mm_Horizontal
R14: 1k; R_Axial_DIN0204_L3.6mm_D1.6mm_P7.62mm_Horizontal
R16: 2.2k; R_Axial_DIN0204_L3.6mm_D1.6mm_P7.62mm_Horizontal
R17: 10; R_Axial_DIN0204_L3.6mm_D1.6mm_P7.62mm_Horizontal
R24: 1K; R_Axial_DIN0204_L3.6mm_D1.6mm_P7.62mm_Horizontal
U1: LM741; CERDIP-8_W7.62mm_SideBrazed_Socket

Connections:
AMS LED +ve: C1.1, C2.1, F1.2, J2.2, J3.2, J4.2, J5.1, J6.1, J7.1, J10.2, R24.1, U1.7 (V+)
AMS LED -ve: J3.1, R3.1
AMS LED IN: J8.2, R1.1, R2.2
BSPD LED -ve: J2.1, R12.1
BSPD LED IN: J8.5, R10.2, R11.1
Brake Light In: J8.4, R21.2, R22.1
Brake light -ve: J7.2, R23.1
GND: C1.2, C2.2, C3.1, D1.1 (K), H1.MP, H2.MP, H3.MP, H4.MP, J1.2, Q1.3 (E), Q2.3 (E), Q3.3 (E), Q4.3 (E), Q5.3 (E), Q6.3 (E), Q7.3 (E), R2.1, R4.1, R7.1, R10.1, R14.1, R18.1, R21.1, R25.1, U1.4 (V-)
IMD LED -ve: J4.1, R6.1
IMD LED IN: J8.1, R4.2, R5.1
unnamed: C3.2, R14.2, R15.2, R17.1
unnamed: D1.2 (A), R24.2
unnamed: F1.1, J1.1
unnamed: Q1.2 (B), R1.2
unnamed: Q1.1 (C), R3.2
unnamed: Q2.2 (B), R5.2
unnamed: Q2.1 (C), R6.2
unnamed: Q3.2 (B), R11.2
unnamed: Q3.1 (C), R12.2
unnamed: Q4.2 (B), R22.2
unnamed: Q4.1 (C), R23.2
unnamed: Q5.2 (B), R19.2
unnamed: Q5.1 (C), R20.2
unnamed: Q6.2 (B), R8.2
unnamed: Q6.1 (C), R9.2
unnamed: Q7.2 (B), R26.2
unnamed: Q7.1 (C), R27.2
unnamed: R13.1, R16.2
unnamed: R16.1, R17.2
unnamed: R15.1, U1.3 (+)
RTD -ve out: J5.2, R20.1
RTD Signal IN: J5.3, R13.2
RTD Signal VCU IN: J5.5, R18.2, R19.1
RTD Signal VCU Out: J5.4, U1.2 (-), U1.6
SDC_Status_in: J10.3, R25.2, R26.1
SDC_status_LED-ve: J10.1, R27.1
VCU LED -ve: J6.2, R9.1
VCU LED IN: J8.3, R7.2, R8.1

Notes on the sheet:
Dashboard LED driver incomming status from vehicle Shutdown circuit
Mounting Holes
Ready to Drive Button signal conditioning
status input from SDC
0V/12V
Power Indicator
RTD in/out
Dashboard LED output
22 AWG wire
Power Port
0V/3.3V
